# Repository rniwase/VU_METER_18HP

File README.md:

# 18 HP Eurorack VU Meter
An 18 HP Eurorack VU meter module using the HIOKI HK-65F.

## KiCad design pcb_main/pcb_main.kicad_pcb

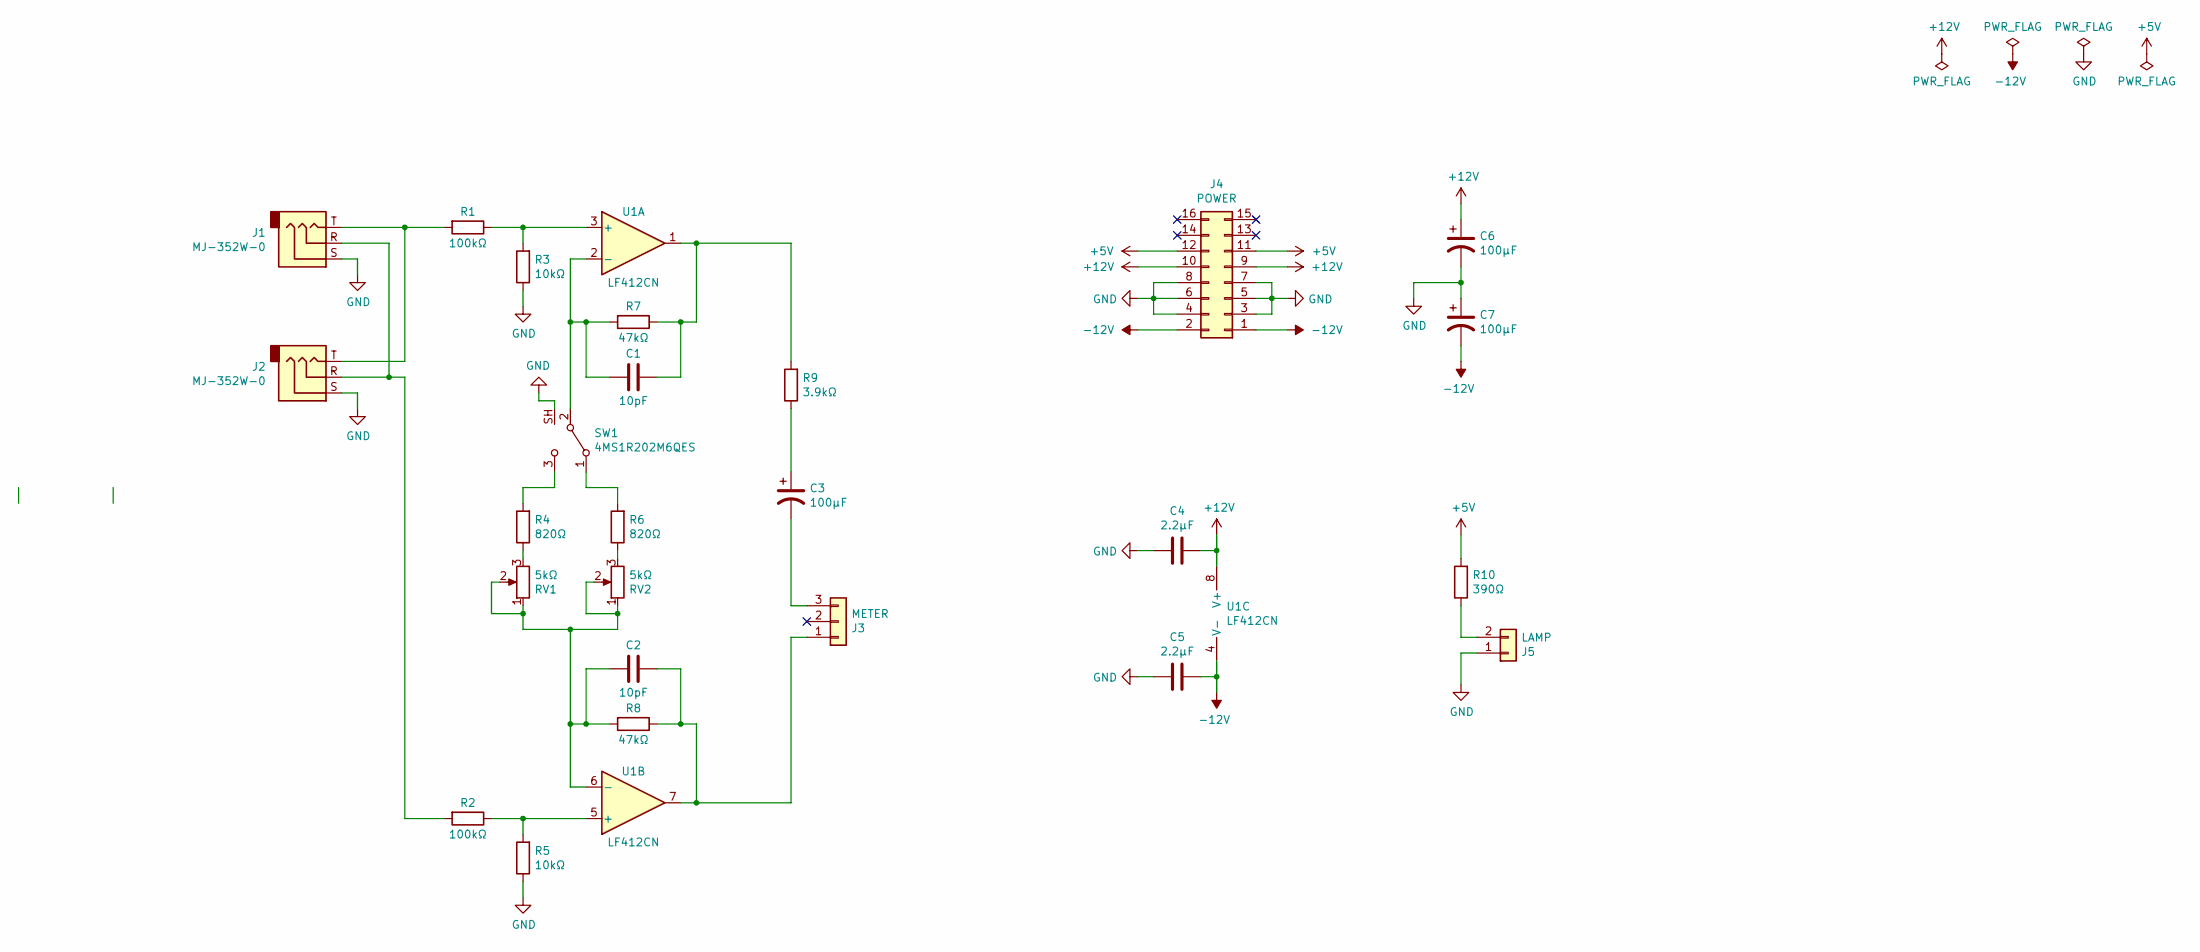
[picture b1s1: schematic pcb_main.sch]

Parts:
C1, C2: 10pF; C_Disc_D3.8mm_W2.6mm_P2.50mm
C3, C6, C7: 100μF; CP_Radial_D6.3mm_P2.50mm
C4, C5: 2.2μF; C_Disc_D4.7mm_W2.5mm_P5.00mm
J1, J2: MJ-352W-0
J3: METER; JST_XH_B3B-XH-A_1x03_P2.50mm_Vertical
J4: POWER; IDC-Header_2x08_P2.54mm_Horizontal
J5: LAMP; JST_XH_B2B-XH-A_1x02_P2.50mm_Vertical
R1, R2: 100kΩ; R_Axial_DIN0207_L6.3mm_D2.5mm_P10.16mm_Horizontal
R3, R5: 10kΩ; R_Axial_DIN0207_L6.3mm_D2.5mm_P10.16mm_Horizontal
R4, R6: 820Ω; R_Axial_DIN0207_L6.3mm_D2.5mm_P10.16mm_Horizontal
R7, R8: 47kΩ; R_Axial_DIN0207_L6.3mm_D2.5mm_P2.54mm_Vertical
R9: 3.9kΩ; R_Axial_DIN0207_L6.3mm_D2.5mm_P10.16mm_Horizontal
R10: 390Ω; R_Axial_DIN0207_L6.3mm_D2.5mm_P10.16mm_Horizontal
RV1, RV2: 5kΩ; Potentiometer_Bourns_3006P_Horizontal
SW1: 4MS1R202M6QES
U1: LF412CN; DIP-8_W7.62mm_LongPads

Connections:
+5V: J4.11, J4.12, R10.2
+12V: C4.1, C6.1, J4.9, J4.10, U1.8 (V+)
-12V: C5.1, C7.2, J4.1, J4.2, U1.4 (V-)
GND: C4.2, C5.2, C6.2, C7.1, J1.S, J2.S, J4.3, J4.4, J4.5, J4.6, J4.7, J4.8, J5.1, R3.1, R5.1, SW1.SH
unnamed: C1.1, R7.1, R9.2, U1.1
unnamed: C1.2, R7.2, SW1.2 (B), U1.2 (-)
unnamed: C2.1, J3.1, R8.1, U1.7
unnamed: C2.2, R8.2, RV1.1, RV1.2, RV2.1, RV2.2, U1.6 (-)
unnamed: C3.1, R9.1
unnamed: C3.2, J3.3
unnamed: J1.R, J2.R, R2.2
unnamed: J1.T, J2.T, R1.2
unnamed: J5.2, R10.1
unnamed: R1.1, R3.2, U1.3 (+)
unnamed: R2.1, R5.2, U1.5 (+)
unnamed: R4.1, RV1.3
unnamed: R4.2, SW1.3 (C)
unnamed: R6.1, RV2.3
unnamed: R6.2, SW1.1 (A)

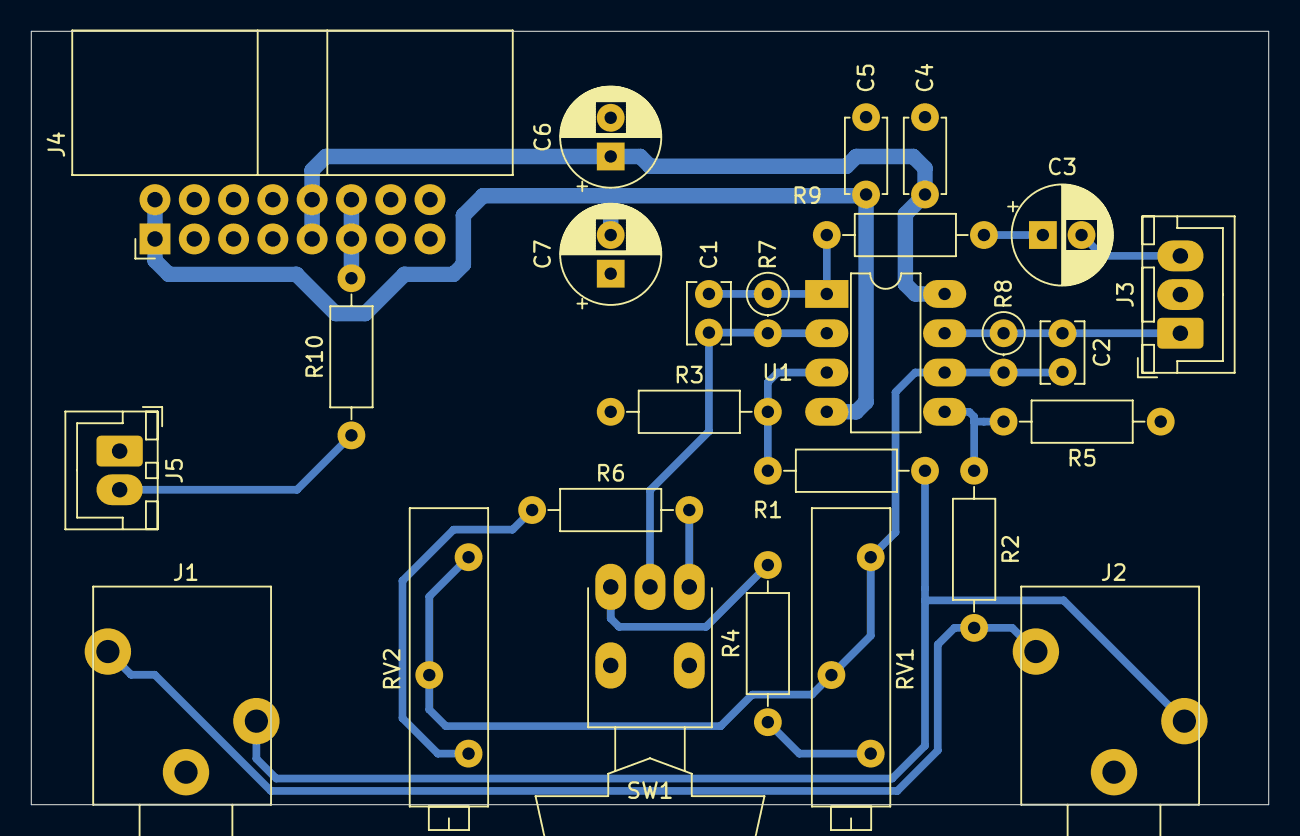
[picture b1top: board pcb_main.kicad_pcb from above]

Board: 2 copper layers, 80.0 x 50.0 mm, 26 parts (0 on the bottom side), 19 nets.

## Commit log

2020-07-14 update pcb_main plot setting, generate gerber and g-code
2020-07-18 add frontpanel gerber and gcode
2020-08-16 add README
2020-12-11 add .gitattributes
